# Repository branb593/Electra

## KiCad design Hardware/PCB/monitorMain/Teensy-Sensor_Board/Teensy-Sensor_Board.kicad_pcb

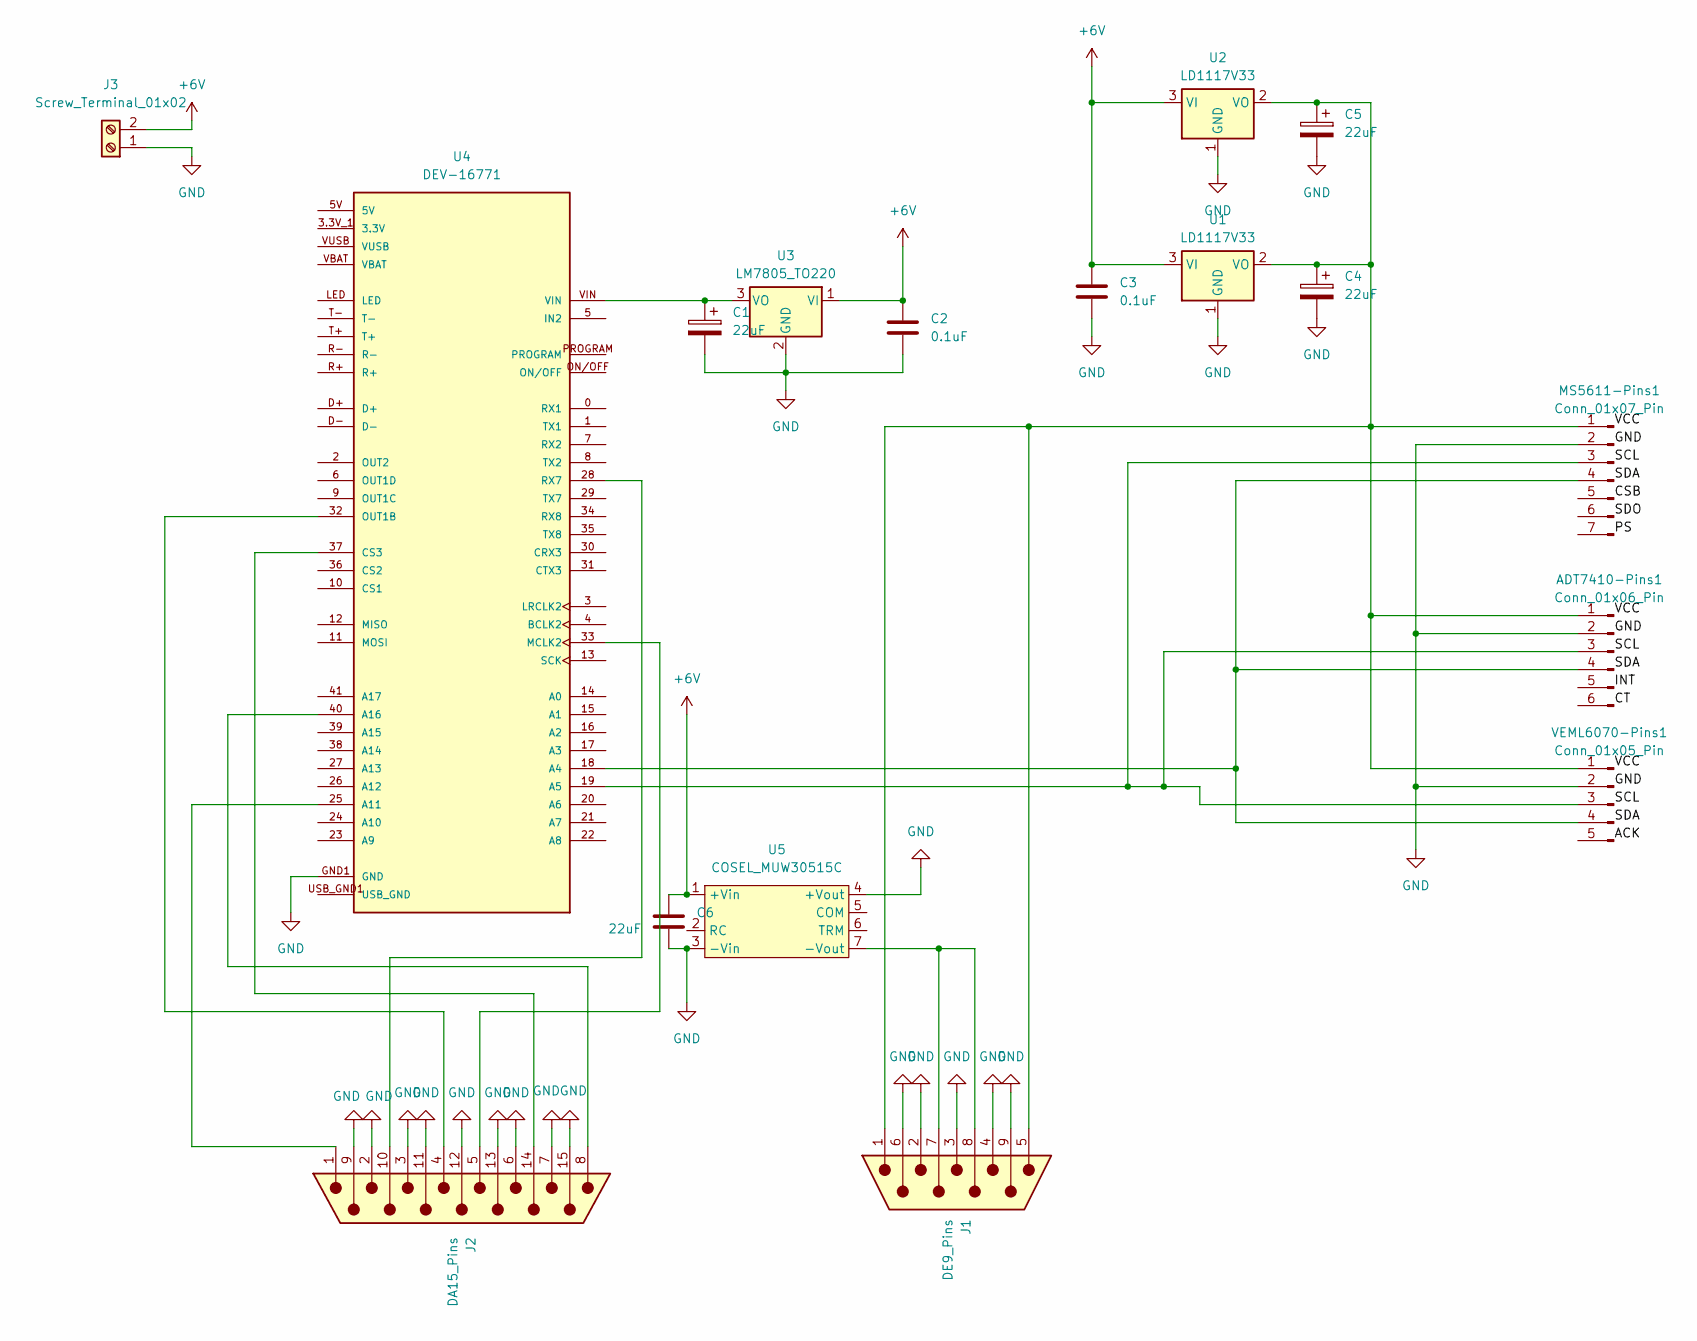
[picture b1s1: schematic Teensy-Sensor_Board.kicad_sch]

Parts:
ADT7410-Pins1: Conn_01x06_Pin; PinHeader_1x06_P1.00mm_Vertical
C1, C4, C5, C6: 22uF; CP_Radial_D4.0mm_P2.00mm
C2, C3: 0.1uF; C_Disc_D3.0mm_W1.6mm_P2.50mm
J1: DE9_Pins; DSUB-9_Pins_Horizontal_P2.77x2.84mm_EdgePinOffset9.90mm_Hou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
J2: DA15_Pins; DSUB-15_Pins_Horizontal_P2.77x2.84mm_EdgePinOffset4.94mm_Ho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
J3: Screw_Terminal_01x02; TerminalBlock_RND_205-00001_1x02_P5.00mm_Horizontal
MS5611-Pins1: Conn_01x07_Pin; PinHeader_1x07_P1.00mm_Vertical
U1, U2: LD1117V33; TO-220-3_Vertical
U3: LM7805_TO220; TO-220-3_Vertical
U4: DEV-16771; MODULE_DEV-16771; PARTREV 4.1
U5: COSEL_MUW30515C; Converter_DC-DC_Cosel_MUW30515C_THT
VEML6070-Pins1: Conn_01x05_Pin; PinHeader_1x05_P1.00mm_Vertical

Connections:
3.3V: U4.3.3V_1 (3.3V), U4.3.3V_2 (3.3V), U4.3.3V_3 (3.3V)
+6V: C2.1, C3.1, C6.1, J3.2, U1.3 (VI), U2.3 (VI), U3.1 (VI), U5.1 (+Vin)
GND: ADT7410-Pins1.2, C1.2, C2.2, C3.2, C4.2, C5.2, C6.2, J1.2, J1.3, J1.4, J1.6, J1.9, J2.2, J2.3, J2.6, J2.7, J2.9, J2.11 (P111), J2.12, J2.13, J2.15, J3.1, MS5611-Pins1.2, U1.1 (GND), U2.1 (GND), U3.2 (GND), U4.GND1 (GND), U4.GND2 (GND), U4.GND3 (GND), U4.GND4 (GND), U4.GND5 (GND), U5.3 (-Vin), U5.4 (+Vout), VEML6070-Pins1.2
unnamed: ADT7410-Pins1.1, C4.1, C5.1, J1.1, J1.5, MS5611-Pins1.1, U1.2 (VO), U2.2 (VO), VEML6070-Pins1.1
unnamed: ADT7410-Pins1.3, MS5611-Pins1.3, U4.19 (A5), VEML6070-Pins1.3
unnamed: ADT7410-Pins1.4, MS5611-Pins1.4, U4.18 (A4), VEML6070-Pins1.4
unnamed: J2.10, U4.28 (RX7)
unnamed: J2.14, U4.37 (CS3)
unnamed: C1.1, U3.3 (VO), U4.VIN
unnamed: J2.1, U4.25 (A11)
unnamed: J2.8, U4.40 (A16)
unnamed: J2.5, U4.33 (MCLK2)
unnamed: J2.4, U4.32 (OUT1B)
unnamed: J1.7, J1.8, U5.7 (-Vout)
USB_GND: U4.USB_GND1 (USB_GND), U4.USB_GND2 (USB_GND)

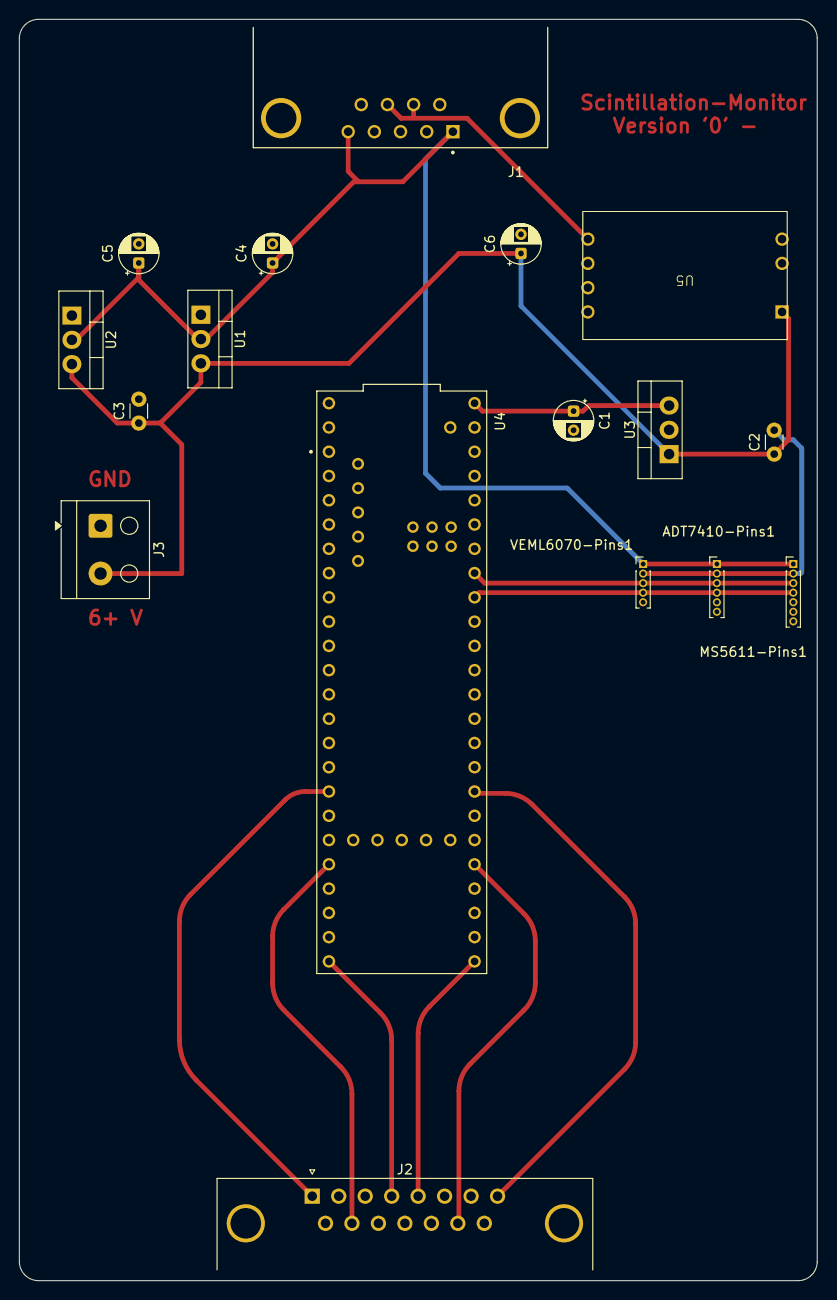
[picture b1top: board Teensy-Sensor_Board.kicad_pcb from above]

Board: 2 copper layers, 83.5 x 132.0 mm, 17 parts (0 on the bottom side), 15 nets.

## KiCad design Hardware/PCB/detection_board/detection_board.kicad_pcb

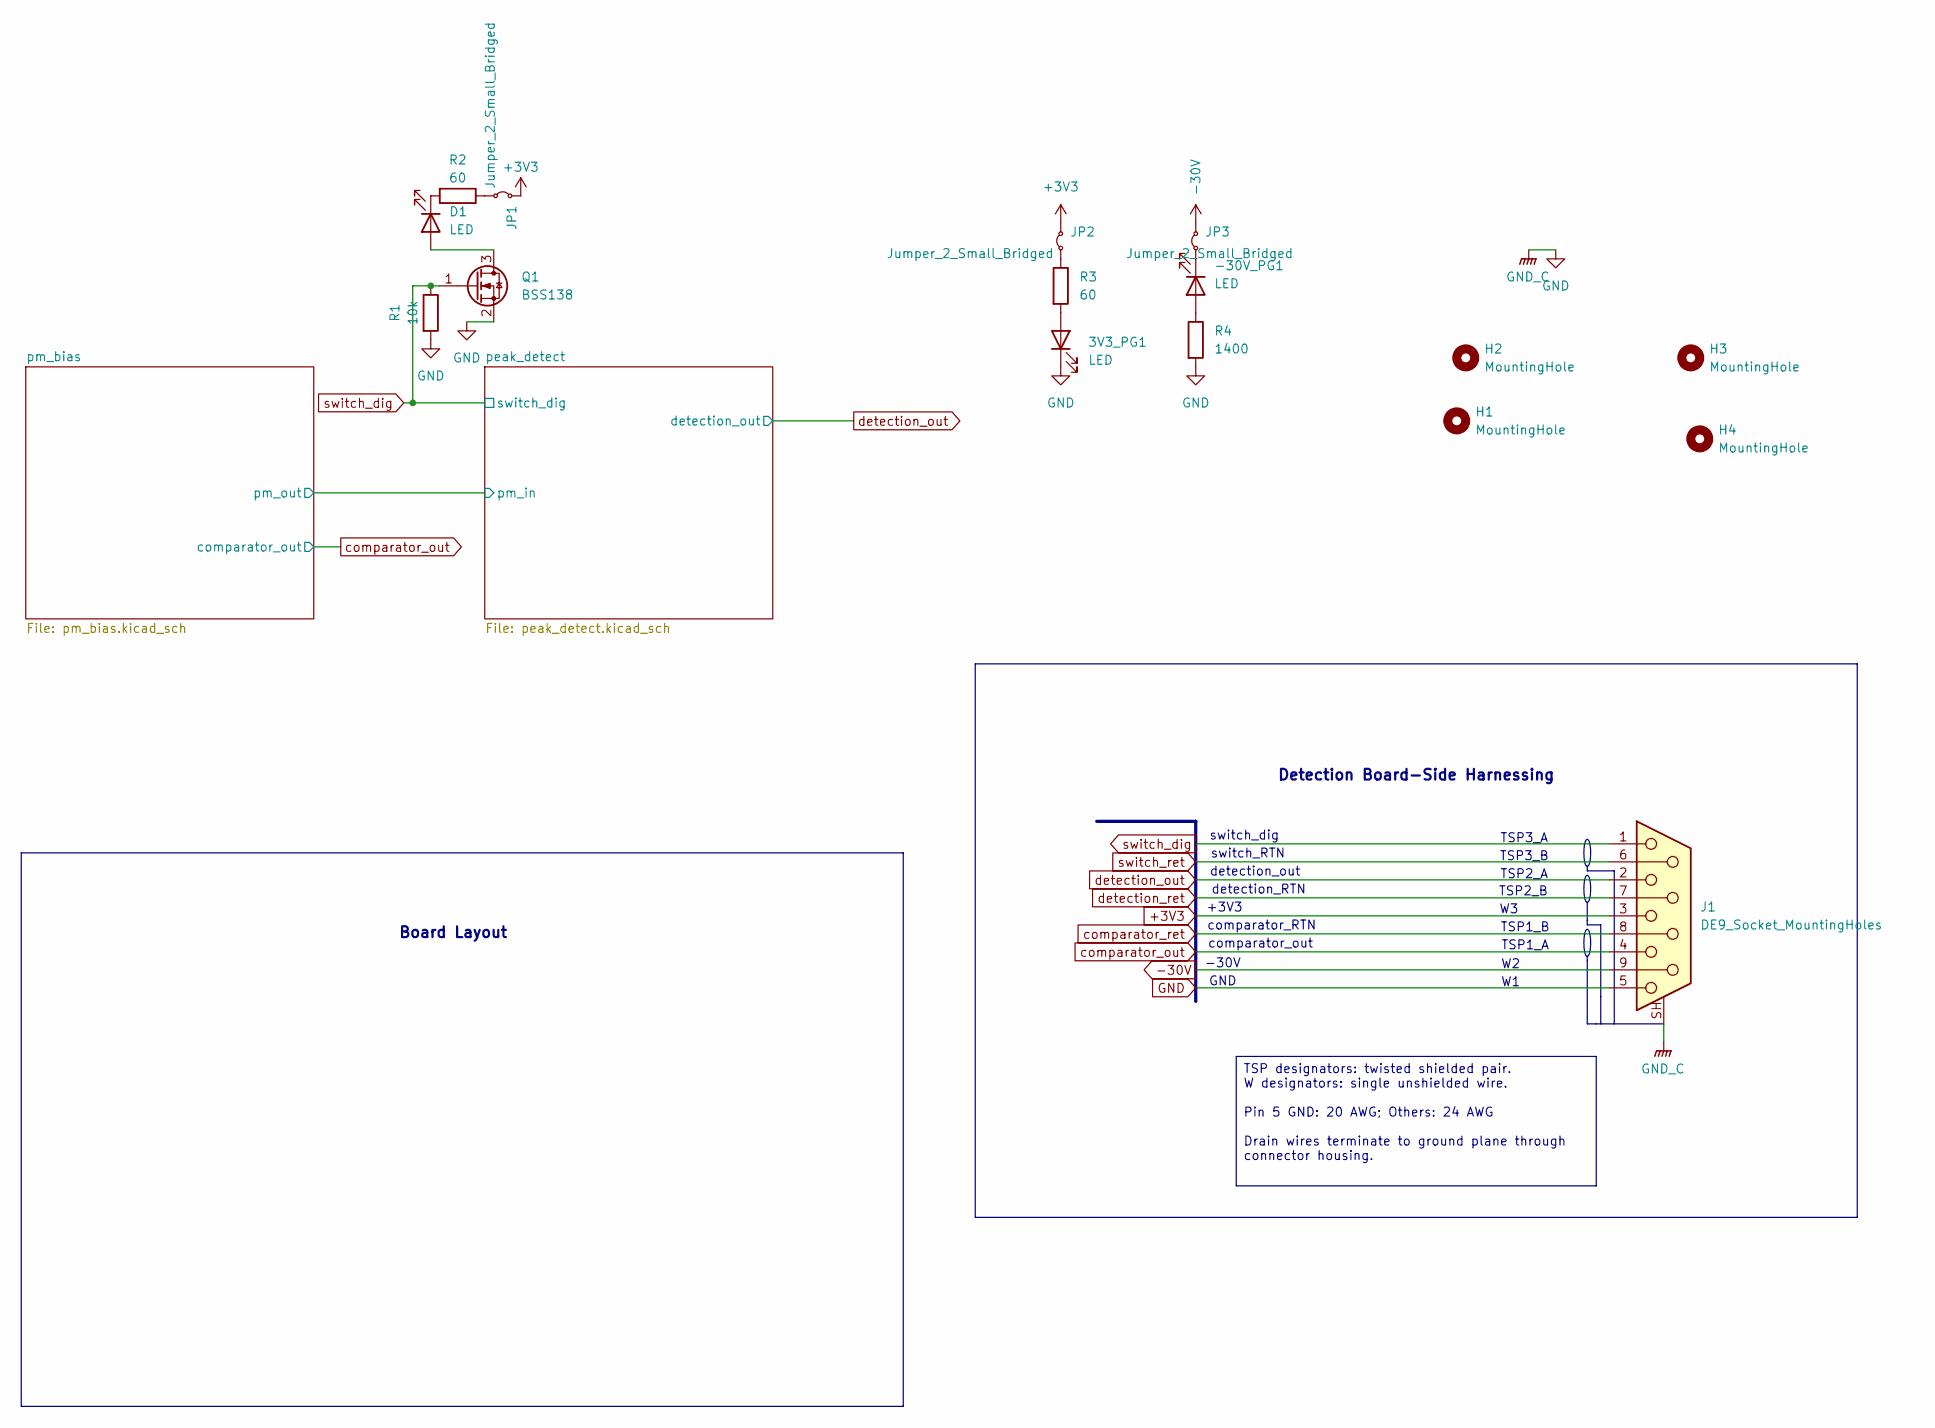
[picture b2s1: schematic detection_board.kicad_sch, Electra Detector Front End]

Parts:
3V3_PG1: LED; LED_0805_2012Metric
-30V_PG1: LED; LED_0805_2012Metric
D1: LED; LED_0805_2012Metric
H1, H2, H3, H4: MountingHole; MountingHole_2.2mm_M2_DIN965_Pad
J1: DE9_Socket_MountingHoles; AMPHENOL_D09P33E4GL00LF
JP1, JP2, JP3: Jumper_2_Small_Bridged; TestPoint_2Pads_Pitch2.54mm_Drill0.8mm
Q1: BSS138; SOT-23
R1: 10k; R_0603_1608Metric
R2, R3: 60; R_0603_1608Metric
R4: 1400; R_0603_1608Metric

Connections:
+3V3: J1.3, JP1.2 (B), JP2.2 (B); also elsewhere on the board
-30V: J1.9, JP3.2 (B); also elsewhere on the board
GND: 3V3_PG1.1 (K), J1.5, J1.6, J1.7, J1.8, J1.SH (PAD), Q1.2 (S), R1.2, R4.2; also elsewhere on the board
unnamed: 3V3_PG1.2 (A), R3.2
unnamed: -30V_PG1.2 (A), R4.1
unnamed: -30V_PG1.1 (K), JP3.1 (A)
unnamed: D1.2 (A), Q1.3 (D)
unnamed: D1.1 (K), R2.2
unnamed: JP1.1 (A), R2.1
unnamed: JP2.1 (A), R3.1
comparator_out: J1.4; also elsewhere on the board
detection_out: J1.2; also elsewhere on the board
switch_dig: J1.1, Q1.1 (G), R1.1; also elsewhere on the board

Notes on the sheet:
GND
TSP1_B
comparator_out
comparator_RTN
Board Layout
TSP2_B
switch_dig
TSP3_A
+3V3
detection_out
TSP1_A
detection_RTN
Detection Board-Side Harnessing
TSP3_B
switch_RTN
-30V
TSP2_A
TSP designators: twisted shielded pair. W designators: single unshielded wire. Pin 5 GND: 20 AWG; Others: 24 AWG Drain wires terminate to ground plane through connector housing.

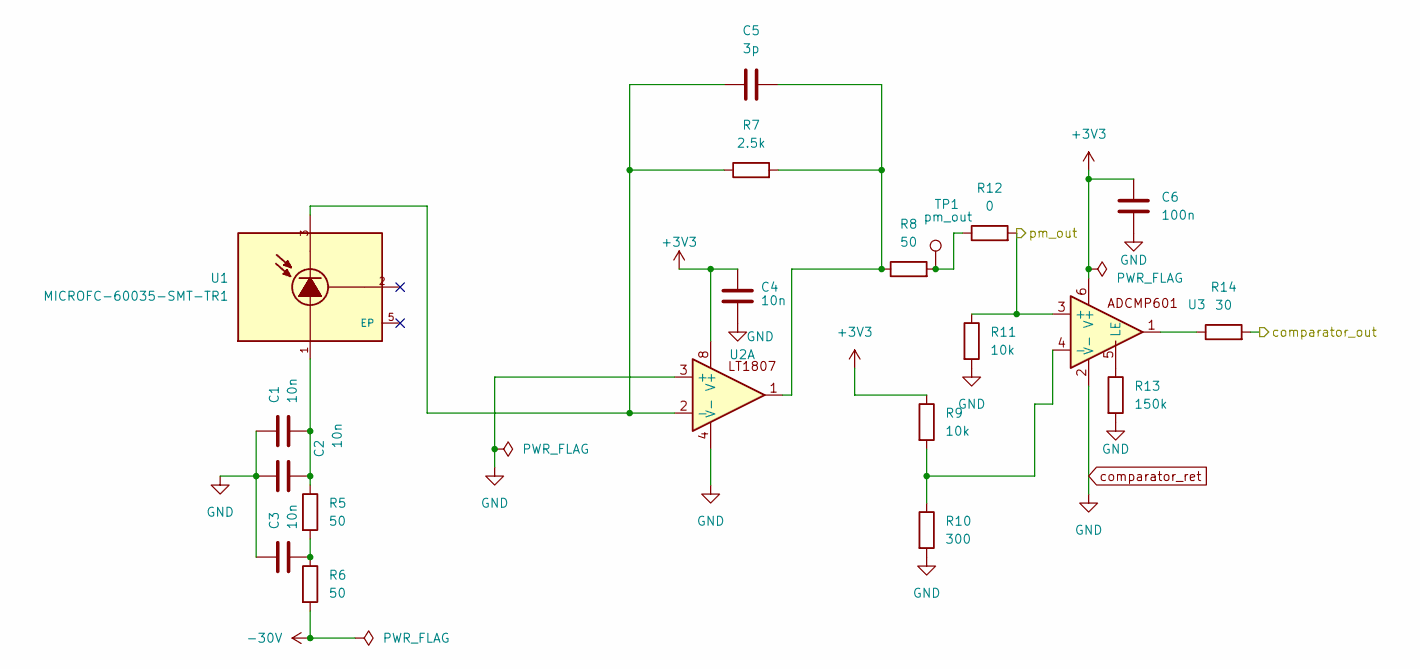
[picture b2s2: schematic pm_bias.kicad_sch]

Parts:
C1, C2, C3, C4: 10n; C_0603_1608Metric
C5: 3p; C_0603_1608Metric
C6: 100n; C_0603_1608Metric
R5, R6, R8: 50; R_0603_1608Metric
R7: 2.5k; R_0603_1608Metric
R9, R11: 10k; R_0603_1608Metric
R10: 300; R_0603_1608Metric
R12: 0; R_0603_1608Metric
R13: 150k; R_0603_1608Metric
R14: 30; R_0603_1608Metric
TP1: pm_out; TestPoint_Pad_1.5x1.5mm
U1: MICROFC-60035-SMT-TR1; XDCR_MICROFC-60035-SMT-TR1; PARTREV 31 JUL 2018
U2: LT1807; SOIC-8_3.9x4.9mm_P1.27mm
U3: ADCMP601; SOT-363_SC-70-6

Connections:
+3V3: C4.1, C6.1, R9.1, U2.8 (V+), U3.6 (V+); also elsewhere on the board
-30V: R6.2; also elsewhere on the board
/peak_detect/pm_in: R11.1, R12.2, U3.3 (+); also elsewhere on the board
GND: C1.1, C2.1, C3.1, C4.2, C6.2, R10.2, R11.2, R13.2, U2.3 (+), U2.4 (V-), U3.2 (V-); also elsewhere on the board
unnamed: C1.2, C2.2, R5.1, U1.1
unnamed: C3.2, R5.2, R6.1
unnamed: C5.2, R7.2, R8.1, U2.1
unnamed: R8.2, R12.1, TP1.1 (1_1)
unnamed: R14.1, U3.1
unnamed: C5.1, R7.1, U1.3, U2.2 (-)
unnamed: R9.2, R10.1, U3.4 (-)
unnamed: R13.1, U3.5 (LE)
comparator_out: R14.2; also elsewhere on the board

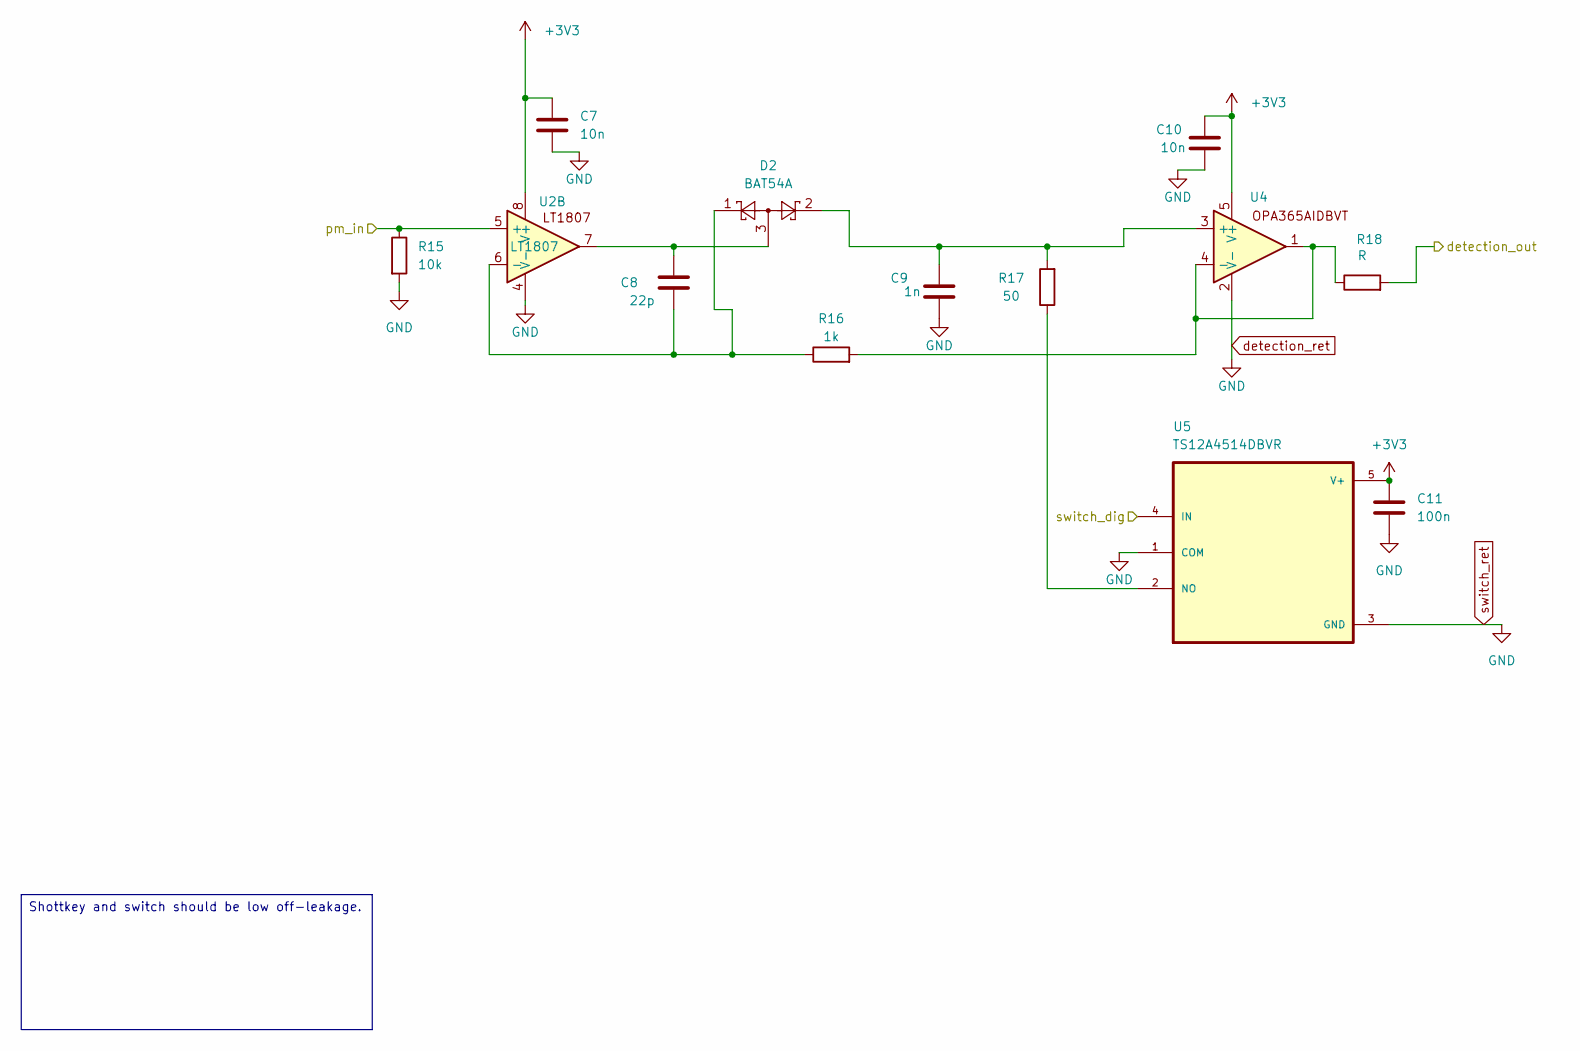
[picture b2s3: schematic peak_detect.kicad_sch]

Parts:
C7, C10: 10n; C_0603_1608Metric
C8: 22p; C_0603_1608Metric
C9: 1n; C_0603_1608Metric
C11: 100n; C_0603_1608Metric
D2: BAT54A; SOT-23
R15: 10k; R_0603_1608Metric
R16: 1k; R_0603_1608Metric
R17: 50; R_0603_1608Metric
R18: R; R_0603_1608Metric
U2: LT1807; SOIC-8_3.9x4.9mm_P1.27mm
U4: OPA365; SOT-23-5_HandSoldering
U5: TS12A4514DBVR; SOT95P280X145-5N

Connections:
+3V3: C7.1, C10.1, C11.1, U2.8 (V+), U4.5 (V+), U5.5 (V+); also elsewhere on the board
/peak_detect/pm_in: R15.1, U2.5 (+); also elsewhere on the board
GND: C7.2, C9.2, C10.2, C11.2, R15.2, U2.4 (V-), U4.2 (V-), U5.1 (COM), U5.3 (GND); also elsewhere on the board
unnamed: C8.1, D2.3, U2.7
unnamed: C8.2, D2.1, R16.1, U2.6 (-)
unnamed: C9.1, D2.2, R17.2, U4.3 (+)
unnamed: R16.2, R18.1, U4.1, U4.4 (-)
unnamed: R17.1, U5.2 (NO)
detection_out: R18.2; also elsewhere on the board
switch_dig: U5.4 (IN); also elsewhere on the board

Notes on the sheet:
Shottkey and switch should be low off-leakage.

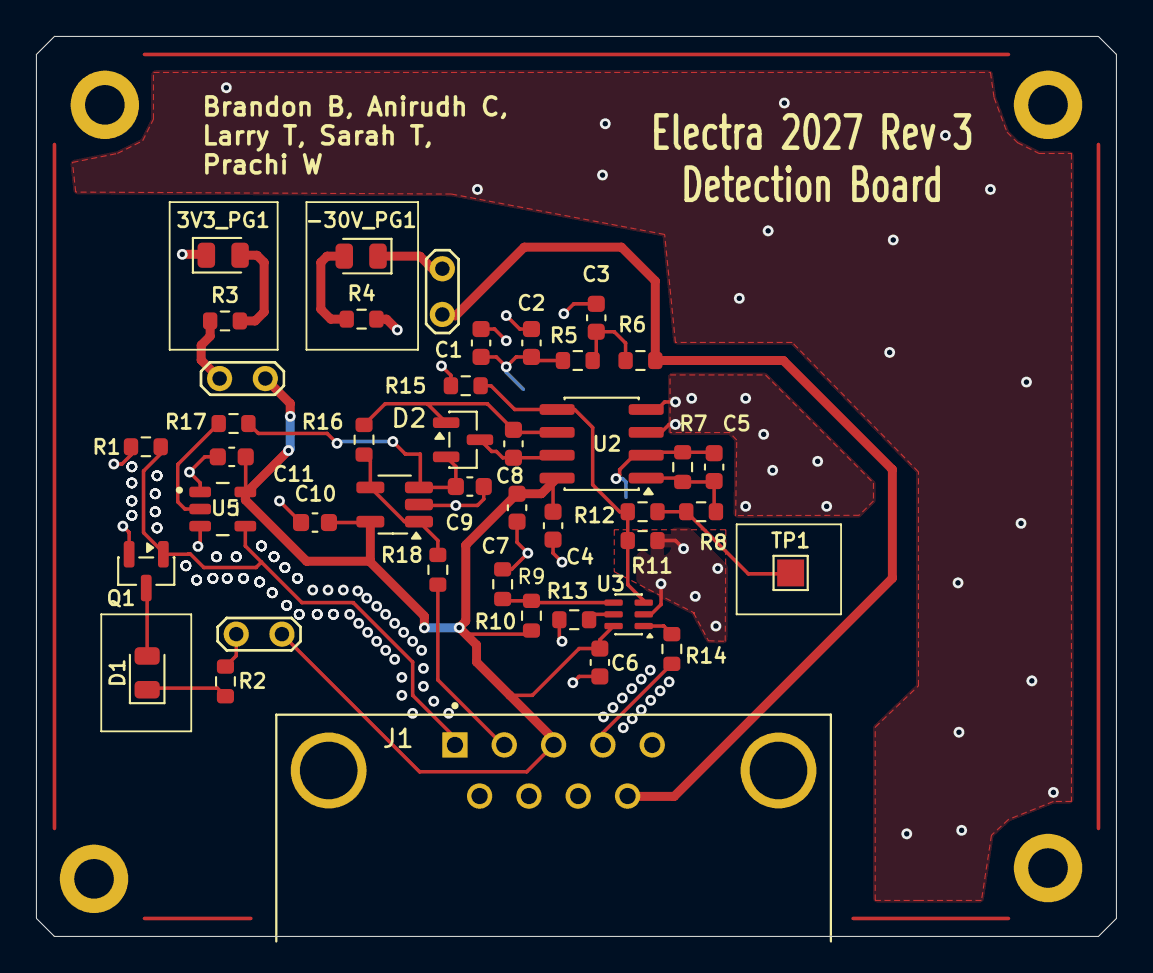
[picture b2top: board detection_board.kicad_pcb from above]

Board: 2 copper layers, 60.0 x 50.0 mm, 48 parts (1 on the bottom side), 27 nets.
